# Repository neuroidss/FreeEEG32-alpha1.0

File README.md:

# use new version: FreeEEG32 + alpha1.5
New version https://github.com/neuroidss/FreeEEG32-alpha1.5

# old FreeEEG32 alpha1.0 -- alpha test failed, don't work without wired bug fixes

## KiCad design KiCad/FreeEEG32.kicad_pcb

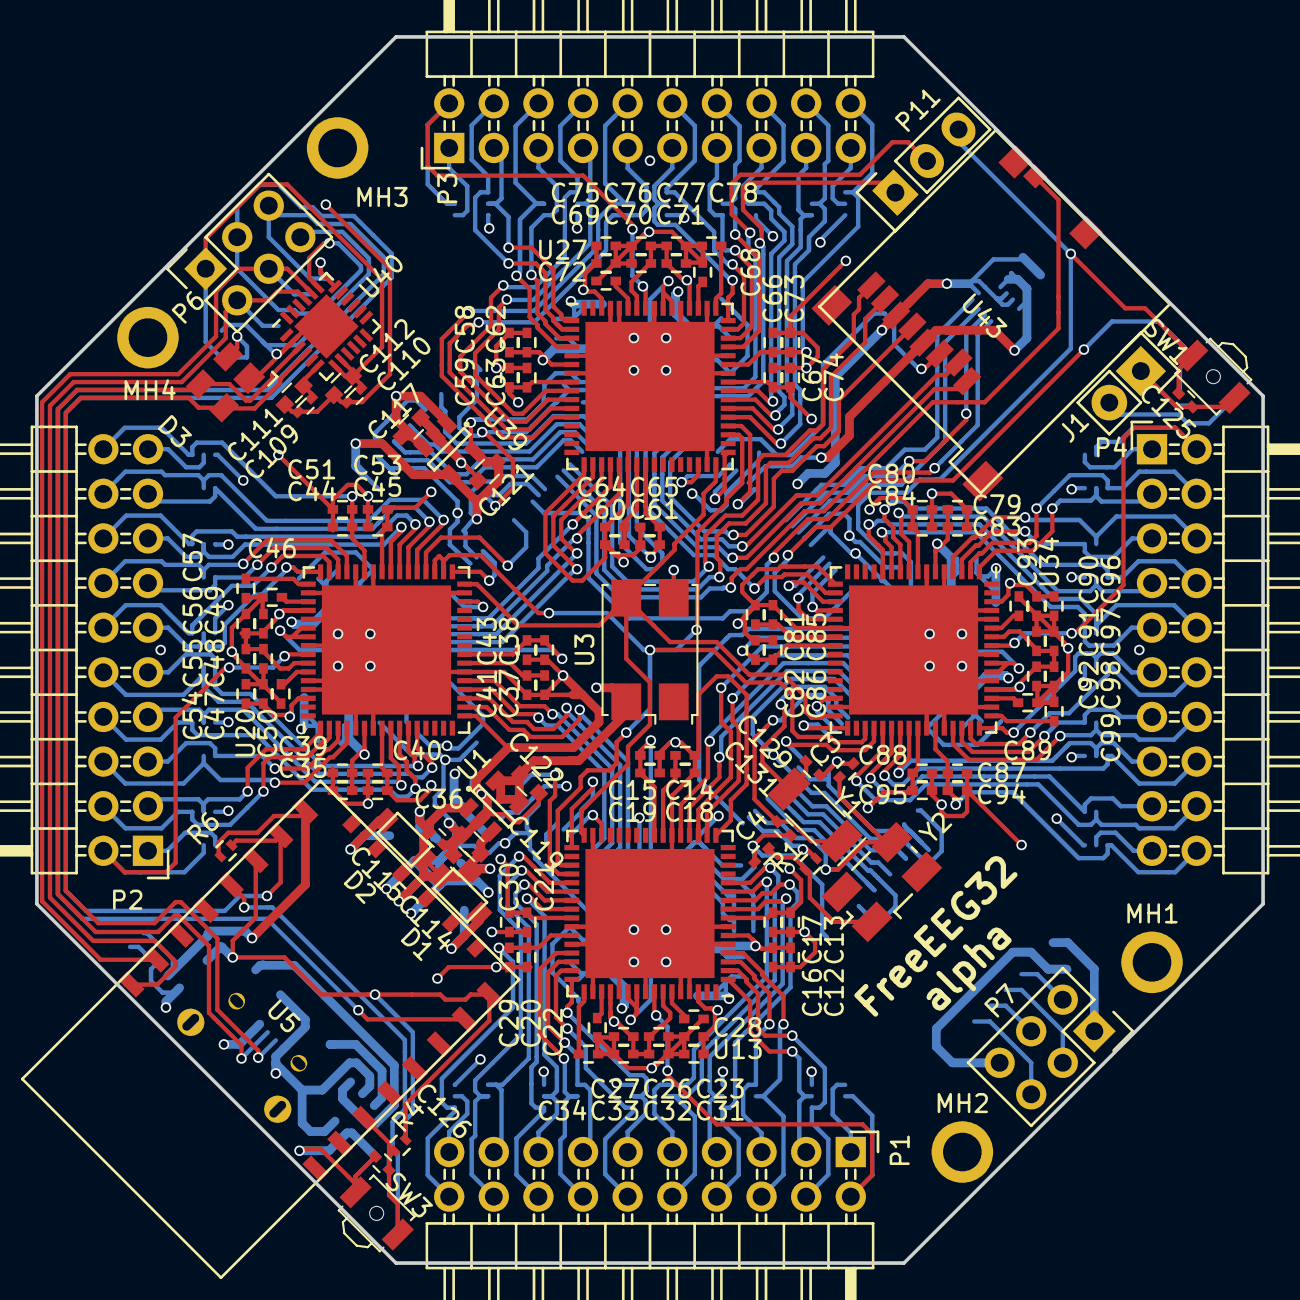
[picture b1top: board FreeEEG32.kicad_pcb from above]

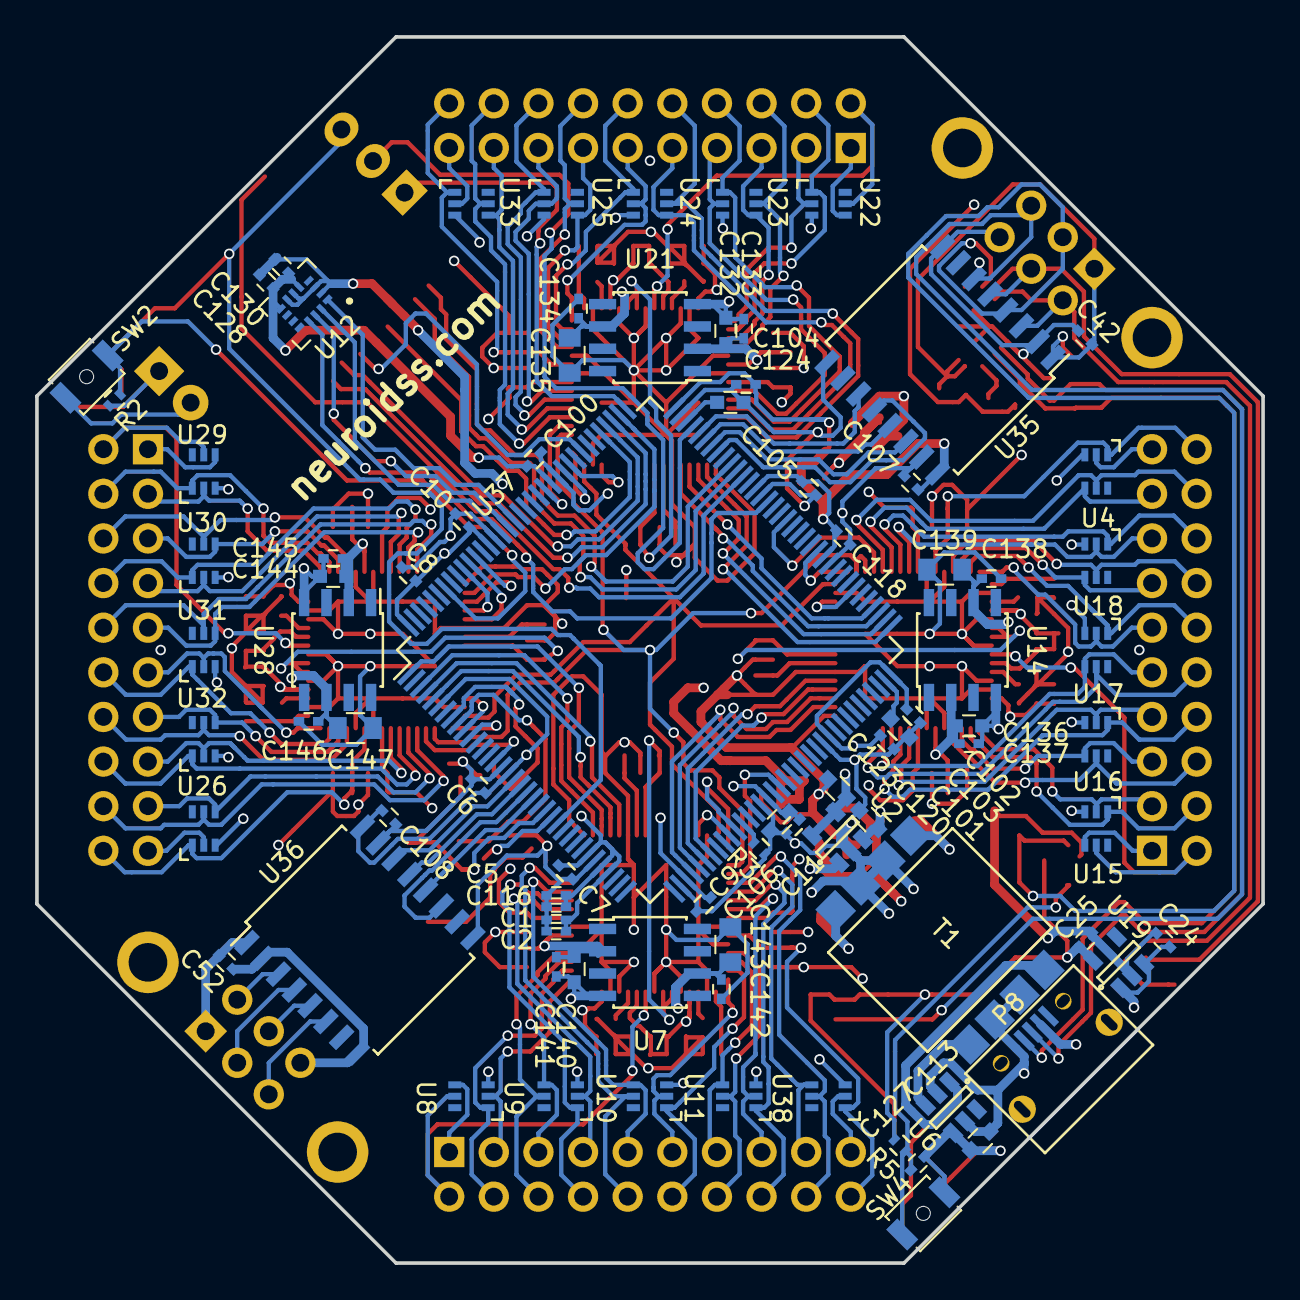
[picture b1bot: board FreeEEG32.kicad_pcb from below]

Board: 4 copper layers, 69.8 x 69.8 mm, 217 parts (85 on the bottom side), 177 nets.

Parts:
C1, C5, C6, C7, C8, C9, C10, C11, C16, C17, C18, C19, C20, C21, C22, C23, C24, C26, C27, C28, C34, C39, C40, C41, C42, C43, C44, C45, C46, C47, C48, C49, C50, C52, C57, C62, C63, C64, C65, C66, C67, C68, C69, C70, C71, C72, C78, C83, C84, C85, C86, C87, C88, C89, C90, C91, C92, C93, C99, C100, C101, C103, C104, C105, C107, C108, C109, C110, C115, C118, C125, C126, C127, C128, C130, C133, C134, C137, C138, C141, C142, C145, C146: 100n; C_0402
C2, C12, C13, C14, C15, C25, C29, C30, C31, C32, C33, C35, C36, C37, C38, C51, C53, C54, C55, C56, C58, C59, C60, C61, C73, C74, C75, C76, C77, C79, C80, C81, C82, C94, C95, C96, C97, C98, C116: 1u; C_0402
C3, C129: CL1; C_0402
C4, C131: CL2; C_0402
C102, C117, C119, C120, C121, C122, C123, C124: 2.2u; C_0603
C106, C111, C112: 4.7u; C_0603
C113, C114, C132, C136, C140, C144: 10u; C_0603
C135, C139, C143, C147: 22u; C_0805
D1, D2: D_Schottky_SMD; SOD−123
D3: SP0503BAHTG; SOT-143
J1: CONN_01X02; Socket_Strip_Straight_1x02
MH1, MH2, MH3, MH4: MountingHole_2.2mm_M2_ISO7380_Pad
P1, P2, P3, P4: CONN_02X10; Pin_Header_Angled_2x10
P6, P7: CONN_02X03; Socket_Strip_Straight_2x03
P8: USB_B; USB_Micro-B_circular
P11: CONN_01X03; Socket_Strip_Straight_1x03
R1: R_EXT; R_0402
R2, R3, R4, R5, R6: 47k; R_0402
SW1: NRST; SW_SPST_B3U-3000P-B
SW2: BOOT0; SW_SPST_B3U-1000P
SW3: BOOT0; SW_SPST_B3U-3000P-B
SW4: BOOT_WIFI; SW_SPST_B3U-1000P
T1: da2303
U1, U2, U39: ADP7118AUJZ-3.3; SOT-23-5
U3: 8.192MHz; Crystal_SMD_7050-4pin_7.0x5.0mm
U4, U8, U9, U10, U11, U15, U16, U17, U18, U22, U23, U24, U25, U26, U29, U30, U31, U32, U33, U38: TPD4E1B06; SC-70-6
U5: ESP-12F; ESP-12E
U6: SN6505A; SOT-23-6
U7, U14, U21, U28: ADR4525; SOIC-8_3.9x4.9mm_Pitch1.27mm
U12: LSM6DS3; LGA-14L_2.5x3mm_Pitch0.5mm
U13, U20, U27, U34: AD7770; QFN-64-1EP_9x9mm_Pitch0.5mm
U19: TLV73333PDBVT; SOT-23-5
U35: ADUM1402BRWZ; SOIC-16_7.5x10.3mm_Pitch1.27mm
U36: ISO7341c_spi; SOIC-16_7.5x10.3mm_Pitch1.27mm
U37: STM32F427ZI_4side_short; LQFP-144_20x20mm_Pitch0.5mm
U40: CP2102N-A01-GQFN24; QFN-24-1EP_4x4mm_Pitch0.5mm
U43: 473521001
Y1: 32768Hz; Crystal_SMD_MicroCrystal_CC4V-T1A-2pin_5.0x1.9mm
Y2: 8MHz; Crystal_SMD_5032_4Pads

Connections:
/ADC1/AIN0+: P2.4, U15.1, U20.2
/ADC1/AIN0-: P2.3, U15.2, U20.1
/ADC1/AIN1+: P2.6, U16.5, U20.4
/ADC1/AIN1-: P2.5, U16.4, U20.3
/ADC1/AIN2+: P2.8, U16.1, U20.10
/ADC1/AIN2-: P2.7, U16.2, U20.9
/ADC1/AIN3+: P2.10, U17.5, U20.12
/ADC1/AIN3-: P2.9, U17.4, U20.11
/ADC1/AIN4+: P2.12, U17.1, U20.47
/ADC1/AIN4-: P2.11, U17.2, U20.48
/ADC1/AIN5+: P2.14, U18.5, U20.45
/ADC1/AIN5-: P2.13, U18.4, U20.46
/ADC1/AIN6+: P2.16, U18.1, U20.39
/ADC1/AIN6-: P2.15, U18.2, U20.40
/ADC1/AIN7+: P2.18, U4.5, U20.37
/ADC1/AIN7-: P2.17, U4.4, U20.38
/ADC1/REF1+: C36.1, C40.1, C45.2, C53.2, C138.2, C139.2, U14.6, U20.8, U20.41
/ADC1/REF_OUT: C57.2, U20.49
/ADC1/VCM: P2.2, U15.5, U20.57
/ADC2/AIN0+: P3.4, U22.1, U27.2
/ADC2/AIN0-: P3.3, U22.2, U27.1
/ADC2/AIN1+: P3.6, U23.5, U27.4
/ADC2/AIN1-: P3.5, U23.4, U27.3
/ADC2/AIN2+: P3.8, U23.1, U27.10
/ADC2/AIN2-: P3.7, U23.2, U27.9
/ADC2/AIN3+: P3.10, U24.5, U27.12
/ADC2/AIN3-: P3.9, U24.4, U27.11
/ADC2/AIN4+: P3.12, U24.1, U27.47
/ADC2/AIN4-: P3.11, U24.2, U27.48
/ADC2/AIN5+: P3.14, U25.5, U27.45
/ADC2/AIN5-: P3.13, U25.4, U27.46
/ADC2/AIN6+: P3.16, U25.1, U27.39
/ADC2/AIN6-: P3.15, U25.2, U27.40
/ADC2/AIN7+: P3.18, U27.37, U33.5
/ADC2/AIN7-: P3.17, U27.38, U33.4
/ADC2/REF1+: C59.1, C63.1, C67.2, C74.2, C134.2, C135.2, U21.6, U27.8, U27.41
/ADC2/REF_OUT: C78.2, U27.49
/ADC2/VCM: P3.2, U22.5, U27.57
/ADC3/AIN0+: P4.4, U29.1, U34.2
/ADC3/AIN0-: P4.3, U29.2, U34.1
/ADC3/AIN1+: P4.6, U30.5, U34.4
/ADC3/AIN1-: P4.5, U30.4, U34.3
/ADC3/AIN2+: P4.8, U30.1, U34.10
/ADC3/AIN2-: P4.7, U30.2, U34.9
/ADC3/AIN3+: P4.10, U31.5, U34.12
/ADC3/AIN3-: P4.9, U31.4, U34.11
/ADC3/AIN4+: P4.12, U31.1, U34.47
/ADC3/AIN4-: P4.11, U31.2, U34.48
/ADC3/AIN5+: P4.14, U32.5, U34.45
/ADC3/AIN5-: P4.13, U32.4, U34.46
/ADC3/AIN6+: P4.16, U32.1, U34.39
/ADC3/AIN6-: P4.15, U32.2, U34.40
/ADC3/AIN7+: P4.18, U26.5, U34.37
/ADC3/AIN7-: P4.17, U26.4, U34.38
/ADC3/REF1+: C80.1, C84.1, C88.2, C95.2, C146.2, C147.2, U28.6, U34.8, U34.41
/ADC3/REF_OUT: C99.2, U34.49
/ADC3/VCM: P4.2, U29.5, U34.57
/ADC4/AIN0+: P1.4, U8.1, U13.2
/ADC4/AIN0-: P1.3, U8.2, U13.1
/ADC4/AIN1+: P1.6, U9.5, U13.4
/ADC4/AIN1-: P1.5, U9.4, U13.3
/ADC4/AIN2+: P1.8, U9.1, U13.10
/ADC4/AIN2-: P1.7, U9.2, U13.9
/ADC4/AIN3+: P1.10, U10.5, U13.12
/ADC4/AIN3-: P1.9, U10.4, U13.11
/ADC4/AIN4+: P1.12, U10.1, U13.47
/ADC4/AIN4-: P1.11, U10.2, U13.48
/ADC4/AIN5+: P1.14, U11.5, U13.45
/ADC4/AIN5-: P1.13, U11.4, U13.46
/ADC4/AIN6+: P1.16, U11.1, U13.39
/ADC4/AIN6-: P1.15, U11.2, U13.40
/ADC4/AIN7+: P1.18, U13.37, U38.5
/ADC4/AIN7-: P1.17, U13.38, U38.4
/ADC4/REF1+: C13.1, C17.1, C21.2, C30.2, C142.2, C143.2, U7.6, U13.8, U13.41
/ADC4/REF_OUT: C34.2, U13.49
/ADC4/VCM: P1.2, U8.5, U13.57
AD1_DRDY: U20.30, U37.79
AD1_RESET: U20.36, U37.90
AD1_START: U20.33, U37.85
AD1_SYNC_IN: U13.35, U20.34, U20.35, U27.35, U34.35
AD2_DRDY: U27.30, U37.118
AD2_RESET: U27.36, U37.122
AD2_START: U27.33, U37.119
AD3_DRDY: U34.30, U37.10
AD3_RESET: U34.36, U37.15
AD3_START: U34.33, U37.11
AD4_DRDY: U13.30, U37.46
AD4_RESET: U13.36, U37.54
AD4_START: U13.33, U37.47
AINREF: P1.1, P2.1, P3.1, P4.1, U8.4, U15.4, U22.4, U29.4
AVDD: C12.1, C16.1, C20.2, C23.1, C26.2, C27.1, C29.2, C31.1, C32.2, C33.1, C35.1, C39.1, C44.2, C47.1, C48.2, C49.1, C51.2, C54.1, C55.2, C56.1, C58.1, C62.1, C66.2, C69.1, C70.2, C71.1, C73.2, C75.1, C76.2, C77.1, C79.1, C83.1, C87.2, C90.1, C91.2, C92.1, C94.2, C96.1, C97.2, C98.1, C123.1, C132.2, C133.2, C136.2, C137.2, C140.2, C141.2, C144.2, C145.2, P1.20, P2.20, P3.20, P4.20, U2.4, U2.5, U4.1, U7.2, U13.6, U13.43, U13.52, U13.58, U13.62, U14.2, U20.6, U20.43, U20.52, U20.58, U20.62, U21.2, U26.1, U27.6, U27.43, U27.52, U27.58, U27.62, U28.2, U33.1, U34.6, U34.43, U34.52, U34.58, U34.62, U38.1
D+_USB: D3.3, P8.3, U40.3
D-_USB: D3.4, P8.2, U40.4
GND: C1.1, C2.1, C3.2, C4.2, C5.1, C6.1, C7.2, C8.1, C9.1, C10.1, C11.1, C12.2, C13.2, C14.2, C15.2, C16.2, C17.2, C18.2, C19.2, C20.1, C21.1, C22.2, C23.2, C26.1, C27.2, C28.1, C29.1, C30.1, C31.2, C32.1, C33.2, C34.1, C35.2, C36.2, C37.2, C38.2, C39.2, C40.2, C41.2, C43.2, C44.1, C45.1, C46.2, C47.2, C48.1, C49.2, C50.1, C51.1, C53.1, C54.2, C55.1, C56.2, C57.1, C58.2, C59.2, C60.2, C61.2, C62.2, C63.2, C64.2, C65.2, C66.1, C67.1, C68.2, C69.2, C70.1, C71.2, C72.1, C73.1, C74.1, C75.2, C76.1, C77.2, C78.1, C79.2, C80.2, C81.2, C82.2, C83.2, C84.2, C85.2, C86.2, C87.1, C88.1, C89.2, C90.2, C91.1, C92.2, C93.1, C94.1, C95.1, C96.2, C97.1, C98.2, C99.1, C100.1, C101.1, C102.2, C103.1, C104.1, C105.1, C106.1, C107.2, C108.2, C114.1, C115.1, C116.1, C117.2, C118.1, C119.2, C120.2, C121.2, C122.2, C123.2, C124.2, C125.1, C128.2, C129.2, C130.2, C131.2, C132.1, C133.1, C134.1, C135.1, C136.1, C137.1, C138.1, C139.1, C140.1, C141.1, C142.1, C143.1, C144.1, C145.1, C146.1, C147.1, J1.1, P1.19, P2.19, P3.19, P4.19, R2.1, R3.2, SW1.2, T1.6, T1.7, U1.2, U2.2, U3.2, U4.2, U4.3, U7.4, U8.3, U9.3, U10.3, U11.3, U12.2, U12.3, U12.6, U12.7, U13.5, U13.7, U13.17, U13.22, U13.31, U13.42, U13.44, U13.50, U13.53, U13.56, U13.60, U13.61, U13.65, U14.4, U15.3, U16.3, U17.3, U18.3, U20.5, U20.7, U20.17, U20.22, U20.31, U20.42, U20.44, U20.50, U20.53, U20.56, U20.60, U20.61, U20.65, U21.4, U22.3, U23.3, U24.3, U25.3, U26.2, U26.3, U27.5, U27.7, U27.17, U27.22, U27.31, U27.42, U27.44, U27.50, U27.53, U27.56, U27.60, U27.61, U27.65, U28.4, U29.3, U30.3, U31.3, U32.3, U33.2, U33.3, U34.5, U34.7, U34.17, U34.22, U34.31, U34.42, U34.44, U34.50, U34.53, U34.56, U34.60, U34.61, U34.65, U35.9, U35.15, U36.9, U36.15, U37.16, U37.31, U37.38, U37.51, U37.61, U37.83, U37.94, U37.107, U37.120, U37.130, U38.2, U38.3, U39.2, U43.6
GND_ISO_SPI: C52.2, P7.6, U36.2, U36.8
GND_ISO_UART: C24.1, C25.1, C42.2, C109.2, C110.1, C111.2, C112.1, C113.2, C126.2, C127.2, D3.1, P6.6, P8.4, R6.1, SW3.2, SW4.2, U5.15, U6.4, U19.2, U35.2, U35.8, U40.2, U40.25
IOVDD: C15.1, C19.1, C38.1, C43.1, C61.1, C65.1, C82.1, C86.1, C122.1, U1.4, U1.5, U3.4, U13.24, U13.54, U13.55, U20.24, U20.54, U20.55, U27.24, U27.54, U27.55, U34.24, U34.54, U34.55
NRST: C125.2, P11.3, SW1.1, U37.25
unnamed: C3.1, U37.23, Y2.2
unnamed: C4.1, R1.1, Y2.1
unnamed: C14.1, C18.1, U13.23
unnamed: C22.1, U13.51
unnamed: C28.2, U13.59
unnamed: C37.1, C41.1, U20.23
unnamed: C46.1, U20.51
unnamed: C50.2, U20.59
unnamed: C60.1, C64.1, U27.23
unnamed: C68.1, U27.51
unnamed: C72.2, U27.59
unnamed: C81.1, C85.1, U34.23
unnamed: C89.1, U34.51
unnamed: C93.2, U34.59
unnamed: C102.1, U37.71
unnamed: C124.1, U37.106
unnamed: C126.1, R4.2, SW3.1, U5.3
unnamed: C127.1, R5.2, SW4.1, U5.18
unnamed: C129.1, U37.8, Y1.2
unnamed: C131.1, U37.9, Y1.1
unnamed: D1.2, T1.8
unnamed: D2.2, T1.5
unnamed: R1.2, U37.24
unnamed: R2.2, SW2.1, U37.138
unnamed: R3.1, U37.48
unnamed: T1.1, U6.3
unnamed: T1.4, U6.1
SDIO_CK: U37.113, U43.5
SDIO_CMD: U37.116, U43.3
SDIO_D0: U37.98, U43.7
SDIO_D1: U37.99, U43.8
SDIO_D2: U37.111, U43.1
SDIO_D3: U37.112, U43.2
SDIO_DETECT: U37.97, U43.9
SPI1_MISO: U20.21, U37.42
SPI1_MOSI: U20.20, U37.43
SPI1_NSS: U20.18, U37.40
SPI1_SCK: U20.19, U37.41
SPI2_MISO: U27.21, U37.75
SPI2_MOSI: U27.20, U37.76
SPI2_NSS: U27.18, U37.73
SPI2_SCK: U27.19, U37.74
SPI3_MISO: U34.21, U37.134
SPI3_MOSI: U34.20, U37.135
SPI3_NSS: U34.18, U37.110
SPI3_SCK: U34.19, U37.133
SPI4_MISO: U13.21, U37.4
SPI4_MOSI: U13.20, U37.5
SPI4_NSS: U13.18, U37.3
SPI4_SCK: U13.19, U37.1
SPI5_MISO: U36.11, U37.20
SPI5_MOSI: U36.12, U37.21
SPI5_NSS: U36.14, U37.18
SPI5_SCK: U36.13, U37.19
SPI6_MISO: U12.1, U37.127
SPI6_MOSI: U12.14, U37.129
SPI6_NSS: U12.12, U37.93
SPI6_SCK: U12.13, U37.128
SPI_MISO_ISO: P7.5, U36.6
SPI_MOSI_ISO: P7.4, U36.5
SPI_NSS_ISO: P7.2, U36.3
SPI_SCK_ISO: P7.3, U36.4
SWCLK: P11.1, U37.109
SWDIO: P11.2, U37.105
UART_CTS_USB: P6.5, U5.7, U35.6, U40.18
UART_RTS_USB: P6.3, R6.2, U5.16, U35.4, U40.19
UART_RX_USB: P6.4, U5.21, U35.5, U40.20
UART_TX_USB: P6.2, U5.22, U35.3, U40.21
USART1_CTS: U35.13, U37.103
USART1_RTS: U35.11, U37.104
USART1_RX: U35.14, U37.102
USART1_TX: U35.12, U37.101
V+: C114.2, C115.2, C117.1, C119.1, C120.1, D1.1, D2.1, U1.1, U1.3, U2.1, U2.3, U39.1, U39.3
V+_ISO_SPI: C52.1, P7.1, U36.1
V+_ISO_UART: C24.2, C42.1, C110.2, C112.2, C113.1, D3.2, P6.1, P8.1, T1.2, T1.3, U6.2, U6.5, U19.1, U19.3, U35.1, U40.7, U40.8
VCC_WIFI: C25.2, R4.1, R5.1, U5.8, U5.17, U19.5
VDD: C1.2, C2.2, C5.2, C6.2, C7.1, C8.2, C9.2, C10.2, C11.2, C100.2, C101.2, C103.2, C104.2, C105.2, C106.2, C107.1, C108.1, C116.2, C118.2, C121.1, C128.1, C130.1, J1.2, SW2.2, U12.5, U12.8, U35.16, U36.16, U37.6, U37.17, U37.30, U37.32, U37.33, U37.39, U37.52, U37.62, U37.72, U37.84, U37.95, U37.108, U37.121, U37.131, U37.144, U39.4, U39.5, U43.4
VDD_USB: C109.1, C111.1, U40.6
XTAL: U3.3, U13.32, U20.32, U27.32, U34.32

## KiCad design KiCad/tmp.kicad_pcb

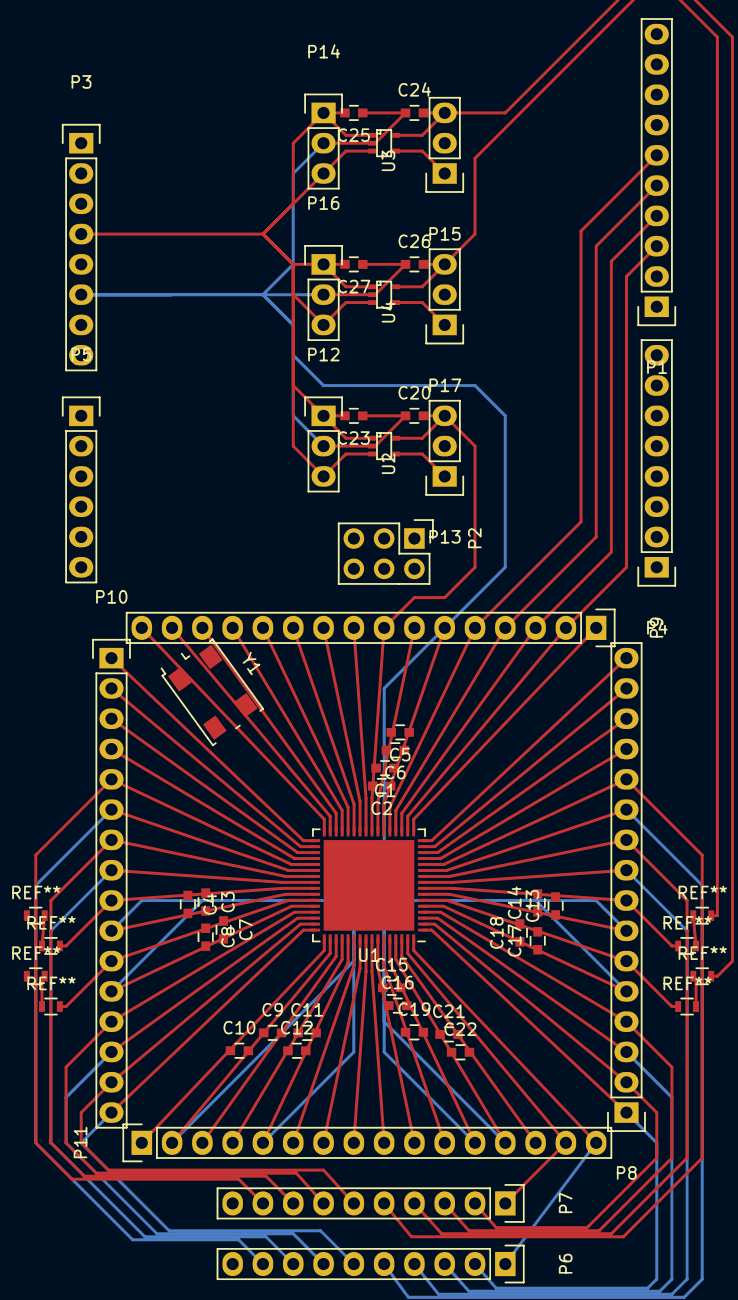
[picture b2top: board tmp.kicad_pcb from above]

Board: 2 copper layers, 49 parts (0 on the bottom side), 50 nets.

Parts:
C1, C5, C13, C17: C 1uF; C_0603
C2, C3, C6, C7, C9, C10, C11, C14, C15, C18, C19, C21: 100pF; C_0603
C4, C8, C12, C16, C20, C22, C23, C24, C25, C26, C27: 1uF; C_0603
P1: DIGITAL(_PWM); Pin_Header_Straight_1x10
P2: ICSP; Pin_Header_Straight_2x03
P3: POWER; Pin_Header_Straight_1x08
P4: DIGITAL(_PWM); Pin_Header_Straight_1x08
P5: ANALOG_IN; Pin_Header_Straight_1x06
P6: CONN_-; Pin_Header_Straight_1x10
P7: CONN_+; Pin_Header_Straight_1x10
P8: CONN_AD7779_1; Pin_Header_Straight_1x16
P9: CONN_AD7779_2; Pin_Header_Straight_1x16
P10: CONN_AD7779_3; Pin_Header_Straight_1x16
P11: CONN_AD7779_4; Pin_Header_Straight_1x16
P12, P13, P14, P15, P16, P17: CONN_01X03; Pin_Header_Straight_1x03
U1: AD7779; LFCSP-64-1EP_9x9mm_Pitch0.5mm
U2, U3: LP5907QMFX-3.3Q1; SC-70-5
U4: LP5907QMFX-2.5Q1; SC-70-5
Y1: 8.192 MHz; SMD0503_4P_Crystal

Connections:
3.3V: C23.2, C25.2, C27.2, P3.4, P12.1, P12.3, P14.1, P14.3, P16.1, P16.3, U2.1, U2.3, U3.1, U3.3, U4.1, U4.3
5V: P2.2, P3.5
ADC_RESET: P1.2, P10.4, U1.36
AIN0+: P7.2, P8.2, U1.2
AIN0-: P6.2, P8.1, U1.1
AIN1+: P7.3, P8.4, U1.4
AIN1-: P6.3, P8.3, U1.3
AIN2+: P7.4, P8.10, U1.10
AIN2-: P6.4, P8.9, U1.9
AIN3+: P7.5, P8.12, U1.12
AIN3-: P6.5, P8.11, U1.11
AIN4+: P7.6, P10.15, U1.47
AIN4-: P6.6, P10.16, U1.48
AIN5+: P7.7, P10.13, U1.45
AIN5-: P6.7, P10.14, U1.46
AIN6+: P7.8, P10.7, U1.39
AIN6-: P6.8, P10.8, U1.40
AIN7+: P7.9, P10.5, U1.37
AIN7-: P6.9, P10.6, U1.38
ALERT: P8.16, U1.16
AREF: P1.8, P3.1
AUXAIN+: P7.1, P11.15, U1.63
AUXAIN-: P6.1, P11.16, U1.64
AVDD: C7.1, C8.1, C11.1, C12.1, C15.1, C16.1, C17.2, C18.2, C21.2, C22.2, C24.2, P8.6, P10.11, P11.4, P11.10, P11.14, P15.3, U1.6, U1.43, U1.52, U1.58, U1.62, U3.5
AVSS: C1.1, C2.1, C3.2, C4.2, C5.1, C6.1, C7.2, C8.2, C9.1, C10.2, C11.2, C12.2, C13.1, C14.1, C15.2, C16.2, C17.1, C18.1, C19.2, C20.1, C21.1, C22.1, C23.1, C24.1, C25.1, C26.1, C27.1, P1.7, P2.6, P3.6, P3.7, P6.10, P7.10, P8.5, P8.7, P9.6, P10.10, P10.12, P11.2, P11.5, P11.12, P11.13, P12.2, P14.2, P16.2, U1.5, U1.7, U1.22, U1.42, U1.44, U1.50, U1.53, U1.60, U1.61, U1.65, U2.2, U3.2, U4.2
CLK_SEL: C1.2, C2.2, C20.2, P9.1, P9.8, P11.6, P11.7, P11.8, P13.3, U1.17, U1.24, U1.54, U1.55, U1.56, U2.5
CS: P1.3, P9.2, U1.18
DCLK: P4.4, P9.13, U1.29
DOUT0: P4.5, P9.12, U1.28
DOUT1: P4.6, P9.11, U1.27
DOUT2: P4.7, P9.10, U1.26
DOUT3: P4.8, P9.9, U1.25
DRDY: P4.3, P9.14, U1.30
GPIO0: P8.13, U1.13
GPIO1: P8.14, U1.14
GPIO2: P8.15, U1.15
unnamed: C5.2, C6.2, U1.23
unnamed: C9.2, U1.51
unnamed: C19.1, U1.59
OUT_VREF: C3.1, C4.1, C13.2, C14.2, C26.2, P8.8, P10.9, P17.3, U1.8, U1.41, U4.5
REF_OUT: C10.1, P11.1, U1.49
SCLK: P1.4, P9.3, U1.19
SDI: P1.5, P9.4, U1.20
SDO: P1.6, P9.5, U1.21
START: P1.1, P10.1, U1.33
SYNC_IN: P10.3, U1.35
SYNC_OUT: P10.2, U1.34
VCM: P11.9, U1.57
XTAL1: P9.15, U1.31, Y1.2
XTAL2: P9.16, U1.32, Y1.1

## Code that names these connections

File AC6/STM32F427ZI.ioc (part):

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Mcu.Name=STM32F427Z(G-I)Tx
Mcu.Package=LQFP144
Mcu.UserName=STM32F427ZITx
PA0/WKUP.Mode=CTS_RTS
PA0/WKUP.Signal=USART2_CTS
PA1.Mode=CTS_RTS
PA1.Signal=USART2_RTS
PA10.Mode=Asynchronous
PA10.Signal=USART1_RX
PA11.Mode=CTS_RTS
PA11.Signal=USART1_CTS
PA12.Mode=CTS_RTS
PA12.Signal=USART1_RTS
PA13.Mode=Serial_Wire
PA13.Signal=SYS_JTMS-SWDIO
PA14.Mode=Serial_Wire
PA14.Signal=SYS_JTCK-SWCLK
PA15.Mode=NSS_Signal_Hard_Output
PA15.Signal=SPI3_NSS
PA2.Mode=Asynchronous
PA2.Signal=USART2_TX
PA3.Mode=Asynchronous
PA3.Signal=USART2_RX
PA4.Mode=NSS_Signal_Hard_Output
PA4.Signal=SPI1_NSS
PA5.Mode=Full_Duplex_Master
PA5.Signal=SPI1_SCK
PA6.Mode=Full_Duplex_Master
PA6.Signal=SPI1_MISO
PA7.Mode=Full_Duplex_Master
PA7.Signal=SPI1_MOSI
PA8.GPIOParameters=GPIO_Label
PA8.GPIO_Label=SDIO_DETECT
PA8.Signal=GPIO_Input
PA9.Mode=Asynchronous
PA9.Signal=USART1_TX
PB12.Mode=NSS_Signal_Hard_Output
PB12.Signal=SPI2_NSS
PB13.Mode=Full_Duplex_Master
PB13.Signal=SPI2_SCK
PB14.Mode=Full_Duplex_Master
PB14.Signal=SPI2_MISO
PB15.Mode=Full_Duplex_Master
PB15.Signal=SPI2_MOSI
PB3.Mode=Full_Duplex_Master
PB3.Signal=SPI3_SCK
PB4.Mode=Full_Duplex_Master
PB4.Signal=SPI3_MISO
PB5.Mode=Full_Duplex_Master
PB5.Signal=SPI3_MOSI
PC10.GPIOParameters=GPIO_PuPd
PC10.GPIO_PuPd=GPIO_PULLUP
PC10.Mode=SD_4_bits_Wide_bus
PC10.Signal=SDIO_D2
PC11.GPIOParameters=GPIO_PuPd
PC11.GPIO_PuPd=GPIO_PULLUP
PC11.Mode=SD_4_bits_Wide_bus
PC11.Signal=SDIO_D3
PC12.GPIOParameters=GPIO_PuPd
PC12.GPIO_PuPd=GPIO_NOPULL
PC12.Mode=SD_4_bits_Wide_bus
PC12.Signal=SDIO_CK
PC8.GPIOParameters=GPIO_PuPd
PC8.GPIO_PuPd=GPIO_PULLUP
PC8.Mode=SD_4_bits_Wide_bus
PC8.Signal=SDIO_D0
PC9.GPIOParameters=GPIO_PuPd
PC9.GPIO_PuPd=GPIO_PULLUP
PC9.Mode=SD_4_bits_Wide_bus
PC9.Signal=SDIO_D1
PD11.Mode=CTS_RTS
PD11.Signal=USART3_CTS
PD12.Mode=CTS_RTS
PD12.Signal=USART3_RTS
PD2.GPIOParameters=GPIO_PuPd
PD2.GPIO_PuPd=GPIO_PULLUP
PD2.Mode=SD_4_bits_Wide_bus
PD2.Signal=SDIO_CMD
PD8.Mode=Asynchronous
PD8.Signal=USART3_TX
PD9.Mode=Asynchronous
PD9.Signal=USART3_RX
PE2.Mode=Full_Duplex_Master
PE2.Signal=SPI4_SCK
PE4.Mode=NSS_Signal_Hard_Output
PE4.Signal=SPI4_NSS
PE5.Mode=Full_Duplex_Master
PE5.Signal=SPI4_MISO
PE6.Mode=Full_Duplex_Master
PE6.Signal=SPI4_MOSI
PF6.Mode=NSS_Signal_Hard_Output
PF6.Signal=SPI5_NSS
PF7.Mode=Full_Duplex_Master
PF7.Signal=SPI5_SCK
PF8.Mode=Full_Duplex_Master
PF8.Signal=SPI5_MISO
PF9.Mode=Full_Duplex_Master
PF9.Signal=SPI5_MOSI
PG12.Mode=Full_Duplex_Master
PG12.Signal=SPI6_MISO
PG13.Mode=Full_Duplex_Master
PG13.Signal=SPI6_SCK
PG14.Mode=Full_Duplex_Master
PG14.Signal=SPI6_MOSI
PG8.Mode=NSS_Signal_Hard_Output
PG8.Signal=SPI6_NSS
PH0/OSC_IN.Mode=HSE-External-Oscillator
PH0/OSC_IN.Signal=RCC_OSC_IN
PH1/OSC_OUT.Mode=HSE-External-Oscillator
PH1/OSC_OUT.Signal=RCC_OSC_OUT
RCC.HSEState=RCC_HSE_ON
RCC.HSE_VALUE=8000000
RCC.SYSCLKFreq_VALUE=180000000
RCC.SYSCLKSource=RCC_SYSCLKSOURCE_PLLCLK

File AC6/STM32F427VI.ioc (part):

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Mcu.Name=STM32F427V(G-I)Tx
Mcu.Package=LQFP100
Mcu.UserName=STM32F427VITx
PA10.Mode=Asynchronous
PA10.Signal=USART1_RX
PA13.Mode=Serial_Wire
PA13.Signal=SYS_JTMS-SWDIO
PA14.Mode=Serial_Wire
PA14.Signal=SYS_JTCK-SWCLK
PA15.Mode=NSS_Signal_Hard_Output
PA15.Signal=SPI3_NSS
PA2.Mode=Asynchronous
PA2.Signal=USART2_TX
PA3.Mode=Asynchronous
PA3.Signal=USART2_RX
PA4.Mode=NSS_Signal_Hard_Output
PA4.Signal=SPI1_NSS
PA5.Mode=Full_Duplex_Master
PA5.Signal=SPI1_SCK
PA6.Mode=Full_Duplex_Master
PA6.Signal=SPI1_MISO
PA7.Mode=Full_Duplex_Master
PA7.Signal=SPI1_MOSI
PA9.Mode=Asynchronous
PA9.Signal=USART1_TX
PB0.GPIOParameters=GPIO_Label
PB0.GPIO_Label=AD_RESET
PB0.Signal=GPIO_Output
PB1.GPIOParameters=GPIO_Label
PB1.GPIO_Label=LED_RED
PB1.Signal=GPIO_Output
PB10.GPIOParameters=GPIO_Label
PB10.GPIO_Label=LED_GREEN
PB10.Signal=GPIO_Output
PB11.GPIOParameters=GPIO_Label
PB11.GPIO_Label=AD2_DRDY
PB11.Signal=GPIO_Input
PB12.Mode=NSS_Signal_Hard_Output
PB12.Signal=SPI2_NSS
PB13.Mode=Full_Duplex_Master
PB13.Signal=SPI2_SCK
PB14.Mode=Full_Duplex_Master
PB14.Signal=SPI2_MISO
PB15.Mode=Full_Duplex_Master
PB15.Signal=SPI2_MOSI
PB3.Mode=Full_Duplex_Master
PB3.Signal=SPI3_SCK
PB4.Mode=Full_Duplex_Master
PB4.Signal=SPI3_MISO
PB5.Mode=Full_Duplex_Master
PB5.Signal=SPI3_MOSI
PB6.GPIOParameters=GPIO_Label
PB6.GPIO_Label=AD3_START
PB6.Signal=GPIO_Output
PB7.GPIOParameters=GPIO_Label
PB7.GPIO_Label=AD3_RESET
PB7.Signal=GPIO_Output
PB8.Mode=mmc_8_bits_Wide_bus
PB8.Signal=SDIO_D4
PB9.Mode=mmc_8_bits_Wide_bus
PB9.Signal=SDIO_D5
PC10.Mode=mmc_8_bits_Wide_bus
PC10.Signal=SDIO_D2
PC11.Mode=mmc_8_bits_Wide_bus
PC11.Signal=SDIO_D3
PC12.Mode=mmc_8_bits_Wide_bus
PC12.Signal=SDIO_CK
PC13.GPIOParameters=GPIO_Label
PC13.GPIO_Label=LED_YELLOW
PC13.Signal=GPIO_Output
PC4.GPIOParameters=GPIO_Label
PC4.GPIO_Label=AD_DRDY
PC4.Signal=GPIO_Input
PC5.GPIOParameters=GPIO_Label
PC5.GPIO_Label=AD_START
PC5.Signal=GPIO_Output
PC6.Mode=mmc_8_bits_Wide_bus
PC6.Signal=SDIO_D6
PC7.Mode=mmc_8_bits_Wide_bus
PC7.Signal=SDIO_D7
PC8.Mode=mmc_8_bits_Wide_bus
PC8.Signal=SDIO_D0
PC9.Mode=mmc_8_bits_Wide_bus
PC9.Signal=SDIO_D1
PD0.Mode=16b-d1
PD0.Signal=FMC_D2
PD1.Mode=16b-d1
PD1.Signal=FMC_D3
PD10.Mode=16b-d1
PD10.Signal=FMC_D15
PD11.Mode=A16_1
PD11.Signal=FMC_A16
PD12.GPIOParameters=GPIO_Label
PD12.GPIO_Label=AD2_START
PD12.Signal=GPIO_Output
PD13.GPIOParameters=GPIO_Label
PD13.GPIO_Label=AD2_RESET
PD13.Signal=GPIO_Output
PD14.Mode=16b-d1
PD14.Signal=FMC_D0
PD15.Mode=16b-d1
PD15.Signal=FMC_D1
PD2.Mode=mmc_8_bits_Wide_bus
PD2.Signal=SDIO_CMD
PD3.GPIOParameters=GPIO_Label
PD3.GPIO_Label=LED_BLUE
PD3.Signal=GPIO_Output
PD4.Mode=Lcd1
PD4.Signal=FMC_NOE
PD5.Mode=Lcd1
PD5.Signal=FMC_NWE
PD6.GPIOParameters=GPIO_Label
PD6.GPIO_Label=AD3_DRDY
PD6.Signal=GPIO_Input
PD7.Mode=NorPsramChipSelect1_1
PD7.Signal=FMC_NE1
PD8.Mode=16b-d1
PD8.Signal=FMC_D13
PD9.Mode=16b-d1
PD9.Signal=FMC_D14
PE0.GPIOParameters=GPIO_Label
PE0.GPIO_Label=AD4_DRDY
PE0.Signal=GPIO_Input
PE1.GPIOParameters=GPIO_Label
PE1.GPIO_Label=AD4_START
PE1.Signal=GPIO_Output
PE10.Mode=16b-d1
PE10.Signal=FMC_D7
PE11.Mode=16b-d1
PE11.Signal=FMC_D8
PE12.Mode=16b-d1
PE12.Signal=FMC_D9
PE13.Mode=16b-d1
PE13.Signal=FMC_D10
PE14.Mode=16b-d1
PE14.Signal=FMC_D11
PE15.Mode=16b-d1
PE15.Signal=FMC_D12
PE2.Mode=Full_Duplex_Master
PE2.Signal=SPI4_SCK
PE3.GPIOParameters=GPIO_Label
PE3.GPIO_Label=AD4_RESET
PE3.Signal=GPIO_Output
PE4.Mode=NSS_Signal_Hard_Output
PE4.Signal=SPI4_NSS
PE5.Mode=Full_Duplex_Master
PE5.Signal=SPI4_MISO
PE6.Mode=Full_Duplex_Master
PE6.Signal=SPI4_MOSI
PE7.Mode=16b-d1
PE7.Signal=FMC_D4
PE8.Mode=16b-d1
PE8.Signal=FMC_D5
PE9.Mode=16b-d1
PE9.Signal=FMC_D6
PH0/OSC_IN.Mode=HSE-External-Oscillator
PH0/OSC_IN.Signal=RCC_OSC_IN
PH1/OSC_OUT.Mode=HSE-External-Oscillator
PH1/OSC_OUT.Signal=RCC_OSC_OUT
RCC.HSE_VALUE=8000000
RCC.SYSCLKFreq_VALUE=180000000
RCC.SYSCLKSource=RCC_SYSCLKSOURCE_PLLCLK
board=STM32F427VI

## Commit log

2017-03-01 FreeEEG32_front.png FreeEEG32_back.png
2017-03-06 FreeEEG32_protocols, ADC-ADC1, FreeEEG32, FreeEEG32_top, FreeEEG32_bottom
2017-03-21 hopefully relevant message about this commit
2017-03-21 gerber
2017-03-25 kicad
2017-03-25 kicad & restructure catalogs
2017-03-25 readme
2018-09-15 Update LICENSE
